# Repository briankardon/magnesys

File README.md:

# Magnesys

A Python-based magnetic field simulator with an interactive 3D visualization GUI.

## Features

### Simulation
- **Exact analytical solutions** for circular loops using complete elliptic integrals (machine precision, no numerical integration)
- **Biot-Savart integration** for arbitrary wire geometries (rounded rectangles, extensible to any shape)
- **Arbitrary orientations** — current loops can be placed and oriented anywhere in 3D space
- **Time-varying fields** — each current source has frequency and phase parameters; field modulated by cos(2πft + φ) at any time t
- **Vectorized computation** — field evaluation works on single points or NumPy meshgrids
- **Extensible geometry** — abstract `CurrentLoop` base class with a registration system for adding new loop shapes

### Visualization
- **Interactive 3D viewer** powered by PyVista + Qt, with pan/rotate/zoom
- **Quiver plot** of the magnetic field with three arrow scaling modes (uniform, logarithmic, linear), selectable via radio buttons
- **Draggable slice plane** — compute and display the field on an arbitrary 2D cross-section
- **Sample paths with 2D plot** — three path types (line segment, polyline, spline) with draggable 3D handles; two plot modes: "B vs. position" (field along path at current time) and "B vs. time" (simulated sensor moving along path); dropdown to select which path is displayed
- **Current direction indicators** — arrowheads on each loop showing the direction of current flow
- **Near-wire filtering** — points too close to the wire (where the thin-wire model diverges) are automatically excluded from visualization and color scaling

### GUI controls
- **Objects tree view** — unified list of loops and sample paths with editable properties (double-click to edit). Vectors expand into individual x/y/z components. Changes update the 3D view in real time.
- **Add/delete objects** — Edit menu to add loops (circular, rounded rectangle, infinite line) and paths (line segment, polyline, spline). Delete or clear all via Edit menu, right-click context menu, or Delete key. Polyline/spline points can be added, deleted, or randomized via right-click.
- **Time slider** — scrub through time to see AC fields oscillate; auto-ranges to one period of the slowest frequency
- **Grid resolution slider** with live spacing readout in cm/mm
- **Auto-update toggle** — disable for expensive simulations, use the Update button manually
- **Auto-scale toggle** — lock 3D color bar, arrow lengths, and 2D y-axis to see time-varying amplitude changes
- **Arrow scaling radio buttons** — switch between uniform, logarithmic (default), and linear

### Project files
- **`.mag` file format** (v3) — human-readable JSON storing simulation, visualization settings, camera position, slice plane state, and multiple sample paths
- **File menu** — Open (Ctrl+O), Save (Ctrl+S), Save As (Ctrl+Shift+S)
- **Export menu** — Export field along path to CSV with configurable sampling interval
- Backward-compatible with v1 (simulation-only) and v2 (single sample path) files

## Supported Geometries

| Type | Class | Field method | Parameters |
|------|-------|-------------|------------|
| Circular loop | `CircularCurrentLoop` | Elliptic integrals (exact) | diameter, center, normal, current, frequency, phase |
| Rounded rectangle | `RoundRectCurrentLoop` | Biot-Savart (numerical) | side_lengths, corner_radius, center, normal, orientation, current, frequency, phase |
| Infinite line | `InfiniteLineCurrent` | Analytical (exact) | center, normal, current, frequency, phase |

## Installation

Requires Python 3.10+.

```bash
py -3.14 -m venv .venv
.venv/Scripts/activate    # Windows
pip install numpy scipy pyvista pyvistaqt PyQt6 pyqtgraph
```

## Usage

### GUI

```bash
# Launch with empty simulation
python magnesys.py

# Open a project file
python magnesys.py demos/helmholtz_coil.mag
```

In the GUI you can:
- **Add loops** via Edit → Add loop → Circular / Rounded rectangle / Infinite line
- **Add sample paths** via Edit → Add path → Line segment / Polyline / Spline
- **Edit properties** by double-clicking values in the Objects tree view
- **Delete objects** by selecting one and pressing Delete (or right-click → Delete)
- **Edit polyline/spline points** — right-click a point for Add before/after, Delete, or Randomize
- **Adjust the field grid** with the resolution slider
- **Enable a slice plane** to see the field on a 2D cross-section (draggable)
- **Show sample paths** to plot Bx, By, Bz, |B| vs distance; select path via dropdown
- **Export field data** along the selected path to CSV via Export → Export field along path
- **Save/open projects** as `.mag` files preserving all settings and camera position

### Python API

```python
import numpy as np
from source import CircularCurrentLoop, RoundRectCurrentLoop, Simulation, Visualizer

# Helmholtz coil pair
R = 0.05
sim = Simulation([
    CircularCurrentLoop(
        diameter=2 * R,
        center=[0, 0, R / 2],
        normal=[0, 0, 1],
        current=1.0,
    ),
    CircularCurrentLoop(
        diameter=2 * R,
        center=[0, 0, -R / 2],
        normal=[0, 0, 1],
        current=1.0,
    ),
])

# Compute field at a point
Bx, By, Bz = sim.magnetic_field_at(0, 0, 0)

# Compute field on a grid
X, Y, Z = np.meshgrid(
    np.linspace(-0.1, 0.1, 50),
    np.linspace(-0.1, 0.1, 50),
    [0.0],
)
Bx, By, Bz = sim.magnetic_field_on_grid(X, Y, Z)

# Open the interactive 3D viewer
Visualizer(sim).show(grid_resolution=8)

# Save / load
sim.save("my_simulation.json")
sim = Simulation.load("my_simulation.json")
```

## Demos

The `demos/` directory contains example scripts and `.mag` project files:

| Demo | Description |
|------|-------------|
| `helmholtz_coil` | Classic Helmholtz pair — nearly uniform field between coils |
| `anti_helmholtz` | Opposing currents — field gradient with zero at center |
| `mixed_geometries` | Circular + rectangular loops in one simulation |
| `tilted_loops` | Three orthogonal coils (3-axis coil system) |
| `rectangular_coil` | Sharp-cornered rectangle with save/load roundtrip |
| `rect_helmholtz_3axis` | Three pairs of rectangular Helmholtz coils |
| `field_along_line` | Sample line with 2D field plot |
| `showcase` | Multiple geometries, path types, and features |
| `ac_gradient_coils` | 3-axis anti-Helmholtz gradient coils at 100/137/173 Hz |
| `inversion_test_1kHz_5A` | 3-axis setup optimized for position inversion (1 kHz, 5A) |

Run any demo as a script or open the `.mag` file:

```bash
python demos/helmholtz_coil.py
python magnesys.py demos/helmholtz_coil.mag
```

## Position Inversion

Magnesys includes a magnetic-field-to-position inversion pipeline for
reconstructing a sensor's trajectory from its magnetometer readings.
This is designed for multi-frequency AC excitation setups (e.g. 3-axis
anti-Helmholtz gradient coils at coprime frequencies), where lock-in
demodulation separates each coil pair's contribution.

### How it works

1. **Lock-in demodulation** extracts each frequency's 3-axis field vector from the time-domain signal
2. **Coarse search** finds the nearest match in a precomputed field table (KD-tree)
3. **Nonlinear refinement** via `scipy.optimize.least_squares` from the coarse estimate
4. **6-DOF mode** jointly solves for position + orientation when the sensor rotates

### Workflow: magnesys → invert.py → magnesys

**1. Open a coil setup** with AC sources:
```bash
python magnesys.py demos/inversion_test_1kHz_5A.mag
```

**2. Create or edit a sample path** — this is the probe trajectory the synthetic sensor will follow.

**3. Export the synthetic signal** via Export → Export field vs. time:
- Select the path, set probe speed, duration, and sampling rate (≥10× highest frequency)
- Optionally check "Apply random sensor rotation" for 6-DOF testing
- Save as CSV (e.g. `my_signal.csv`)

**4. Run the inversion:**
```bash
python invert.py demos/inversion_test_1kHz_5A.mag my_signal.csv --window-periods 30
```
This prints position/orientation error statistics and writes `my_signal_inverted.csv`.

Options:
- `--resolution 35` — finer field table grid (slower, more accurate)
- `--window-periods 30` — demodulation window in periods of the lowest frequency

**5. Import the reconstructed trajectory** back into magnesys:
Edit → Import trajectory CSV → select `my_signal_inverted.csv`

**6. Compare** — the reconstructed trajectory appears alongside the original path in the 3D view.

### Tested accuracy (0.5m cage, MLX90393 sensor noise)

| Mode | Drive current | Position error (median) |
|------|--------------|------------------------|
| 3-DOF (no rotation) | 5 A | 2.2 mm |
| 6-DOF (30° rotation) | 5 A | 4.1 mm |

See `docs/inversion_log.md` for the full experiment history.

### Sensor profiles

The export dialog and `invert.py` both understand named sensor profiles
(`source/sensor_profile.py`).  A profile pairs a noise spectral density
(nT/√Hz) with a max 3-axis ODR (Hz); per-sample σ is computed from
`σ = N₀ · √(fs/2)` with `fs` clamped to the sensor's max ODR.  Picking
a profile in the Export → Field vs. time dialog automatically clamps the
sample-rate spinner and shows the resulting σ live.

| Profile | Tech | Noise (nT/√Hz) | Max ODR (Hz) | Notes |
|---------|------|---------------:|-------------:|-------|
| `ideal` | — | 0 | ∞ | Noiseless reference |
| `MLX90393` | Hall | 150 | 500 | Cannot support 1 kHz lock-in |
| `MLX90394` | Hall | 70 | 1000 | Lower-noise successor |
| `AK09940A` | TMR | 30 | 2500 | Best digital integrated option |
| `MMC5983MA` | AMR | 100 | 1000 | Similar regime to MLX90393 |
| `RM3100` | mag-induct. | 13 | 430 | Lowest noise, but heavy & slow |
| `DRV425x3` | fluxgate | 1.5 | 47000 | Reference-grade; high power |

List from the CLI:
```bash
python invert.py --list-sensors
```

Annotate an inversion run with the expected σ for a given profile:
```bash
python invert.py --sensor AK09940A project.mag signal.csv
```

Numbers are best-effort estimates from public datasheets — refine
against the operating mode (OSR, drive current, cycle count) you
actually plan to use.

### Reproducing experiments

`docs/inversion_log.md` is a chronological log of inversion experiments
(coil-geometry sweeps, frequency/window sweeps, sensor noise, dual-
sensor and trajectory studies). Experiments 1-14 were one-off
development work; the parameters are documented in the log but the
exact scripts weren't committed at the time. Experiments 15 onward have
self-contained, re-runnable scripts under `demos/`.

| Exp | Topic | Reproduce |
|----:|-------|-----------|
|  1  | Initial 3-DOF inversion (12 cm scale)  | no committed script — see log for parameters |
|  2  | Frequency grouping fix                  | no committed script |
|  3  | Window length sweep (stationary)        | no committed script |
|  4  | Moving trace, 3-period window           | no committed script |
|  5  | Current strength scaling                | no committed script |
|  6  | First 6-DOF inversion + SVD init        | no committed script |
|  7  | 4-DOF + IMU tilt                        | no committed script |
|  8  | Cage scale baseline (0.5 m)             | no committed script |
|  9  | Coil geometry sweep                     | no committed script |
| 10  | Multipass inversion                     | no committed script |
| 11  | Excitation frequency sweep              | no committed script |
| 12  | Orientation-first 6-DOF                 | no committed script |
| 13  | Fixed window duration, varying freq.    | no committed script |
| 14  | Noise injection (1 kHz, 0.5 m cage)     | no committed script — was the motivation for `SensorProfile` (Exp 15+) |
| 15  | Sensor-realistic re-run at 1 m cube     | `python demos/experiment_15_sensor_realistic.py` |
| 16  | Analog frontend recovers 1 kHz lock-in  | `python demos/experiment_16_analog_frontend.py` |
| 17  | Smaller cage (0.75 m), same coils       | `python demos/experiment_17_smaller_cage.py` |
| 18  | Dual-magnetometer backpack              | `python demos/experiment_18_dual_magnetometer.py` |
| 19  | Lissajous trajectory, robust 6-DOF init | `python demos/experiment_19_lissajous_trajectory.py` |

Most experiment scripts accept `--quick` for a fast lower-resolution
pass and `--duration N` to override the trajectory length. See each
script's `--help` for the full set of flags.

## Adding New Geometries

For geometries with closed-form field solutions, subclass `CurrentLoop` directly:

```python
@CurrentLoop.register
class MyLoop(CurrentLoop):
    loop_type = "my_loop"
    def magnetic_field(self, x, y, z): ...
    def distance_to_wire(self, x, y, z): ...
    def characteristic_size(self): ...
    def get_path(self, n_points=128): ...
    def to_dict(self): ...
    @classmethod
    def from_dict(cls, data): ...
```

For arbitrary wire shapes, subclass `PathBasedLoop` instead — just implement `get_path()` and serialization, and the Biot-Savart field computation is provided automatically.

## Architecture

```
magnesys.py                      # GUI launcher
invert.py                        # CLI for magnetic → position inversion
source/
    current_loop.py              # Abstract base class + registry
    circular_current_loop.py     # Exact field via elliptic integrals
    infinite_line_current.py     # Exact field for infinite straight wire
    path_based_loop.py           # Biot-Savart base for arbitrary paths
    round_rect_current_loop.py
    path.py                      # SamplePath / LineSegmentPath / PolylinePath / SplinePath
    trajectory.py                # Static 3D trajectory for visualization
    simulation.py                # Loop collection + field computation
    inversion.py                 # Field table, demodulation, position inversion
    sensor_profile.py            # Named sensor profiles (noise SD + max ODR)
    visualization.py             # Qt GUI + PyVista 3D + pyqtgraph 2D
    project.py                   # .mag file I/O
demos/
    *.py                         # Example scripts
    *.mag                        # Loadable project files
docs/
    inversion_log.md             # Experiment history and results
```

## Credits

Developed by **Brian Kardon** and **Claude** (Anthropic).

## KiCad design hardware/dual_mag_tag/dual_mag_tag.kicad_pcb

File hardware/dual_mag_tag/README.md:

# Magnesys Dual-Magnetometer Bird Tag — Schematic Design

This directory contains the schematic-level description of the
dual-magnetometer backpack tag developed in the inversion experiments
(see `docs/inversion_log.md`, Exps. 18-19). The design is the analog
TMR + AD8421 + nRF52832 SAADC chain with a 3 cm baseline between the
two magnetometers.

Files:

- `magnesys_dual_mag_tag.net` — KiCad netlist (S-expression `.net`
  format) listing all components and their net connections. This can
  be imported into KiCad's Pcbnew via *File → Import → Netlist*, or
  used as a reference when capturing the schematic in Eeschema.
- `magnesys_tag.kicad_sym` — KiCad symbol library with 6 custom
  schematic symbols: `AD8421`, `TLV9001`, `MIC5219-3.3YM5`,
  `NVE_AAH002` (single-axis analog GMR/TMR), `TMR_3AXIS_PLACEHOLDER`
  (generic 8-pin), and `nRF52832_MODULE` (13-pin module breakout
  with named pins).
- `README.md` (this file) — human-readable design description and BOM.

### Adding the symbol library to KiCad

1. *Preferences → Manage Symbol Libraries → Project Specific Libraries
   → Add an existing library to the table* (the folder icon).
2. Browse to `magnesys_tag.kicad_sym` and select it.
3. Give it a nickname (e.g., `magnesys_tag`).
4. Click *OK*. The 6 symbols become available under that nickname in
   the symbol chooser.

## High-level architecture

```
                     +--------- 3.7 V Li-ion battery (BT1)
                     |
                  +--+--+
                  | LDO | (U_LDO, 3.3 V)
                  +--+--+
                     |
       VCC = 3.3 V --+--------------+----------+----------+
                                    |          |          |
       REF = VCC/2 --+              |          |          |
                     |          +---+---+  +---+---+  ... (×8)
                     |          | TMR1  |  | AD8421|  ...
                     |          | (3-ax)|  | inamp |
       GND ----------+----------+---+---+  +---+---+  ...
                                |              |
                                |              v
                                | -- AC coup --> bias to REF --> +/-IN
                                |
                                +-- 3 cm baseline -- TMR2 same chain

       6 amp outputs --> R-C anti-alias --> nRF52832 SAADC inputs
                                            P0.02-0.05, P0.28-0.29
```

## Sections of the design

### Power

| Net  | Description                  |
|------|------------------------------|
| VBAT | Raw Li-ion (3.0–4.2 V)       |
| VCC  | LDO output, 3.3 V regulated  |
| GND  | Ground reference             |
| REF  | VCC/2, mid-supply for in-amp |

- `U_LDO` — 3.3 V LDO regulator (e.g., MIC5219-3.3 or ADP7142). Low
  quiescent current matters for battery life.
- `C_IN_LDO`, `C_OUT_LDO` — input and output bulk decoupling (1 µF
  ceramic each).
- `R_REF1`, `R_REF2` — divider from VCC to GND, 10 kΩ each, generates
  REF = VCC/2 ≈ 1.65 V.
- `C_REF` — 100 nF smoothing on the REF node.
- `U_BUF` — TLV9001 (or similar rail-to-rail single op-amp) wired as
  a unity-gain buffer to drive REF with low impedance. Without this,
  the REF node would be 5 kΩ Thevenin and would couple noise/offset
  through the in-amp REF pins.

### Magnetometers (×2)

`U_MAG1` and `U_MAG2` are 8-pin analog TMR 3-axis magnetometer dies
(e.g., NVE AAL024 series — replace with the exact part you choose). Pin
allocation:

| Pin | Net |
|-----|-----|
| 1 (VCC) | VCC |
| 2 (GND) | GND |
| 3 (X+)  | MAG1_XP / MAG2_XP |
| 4 (X−)  | MAG1_XN / MAG2_XN |
| 5 (Y+)  | MAG1_YP / MAG2_YP |
| 6 (Y−)  | MAG1_YN / MAG2_YN |
| 7 (Z+)  | MAG1_ZP / MAG2_ZP |
| 8 (Z−)  | MAG1_ZN / MAG2_ZN |

Decoupling: one 100 nF ceramic per sensor, placed close to its VCC
pin.

PCB layout note (not in netlist): MAG1 and MAG2 should be placed
**3.0 cm apart along the PCB +x axis**, with the same orientation. PCB
position tolerance ~0.1 mm is well below the inversion's sensitivity
to the offset.

### Per-channel analog frontend (×6)

Six identical channels, one per (sensor, axis): MAG1_X, MAG1_Y, MAG1_Z,
MAG2_X, MAG2_Y, MAG2_Z. For channel `n`:

| Designator       | Function           | Value     |
|------------------|--------------------|-----------|
| `C_AC{n}P`       | AC-coupling cap on +IN leg | 1 µF |
| `C_AC{n}N`       | AC-coupling cap on −IN leg | 1 µF |
| `R_BIAS{n}P`     | +IN bias to REF    | 100 kΩ    |
| `R_BIAS{n}N`     | −IN bias to REF    | 100 kΩ    |
| `U_AMP{n}`       | AD8421 in-amp      |           |
| `R_GAIN{n}`      | Gain resistor (RG) | 100 Ω → G ≈ 100 |
| `C_AMP{n}`       | Amp decoupling     | 100 nF    |
| `R_AA{n}`        | Anti-alias R       | 10 kΩ     |
| `C_AA{n}`        | Anti-alias C       | 1 nF      |

Signal chain per channel:

```
MAGn_(axis)P --[C_AC*P]--+-- AD8421 +IN
                         |
                         +--[R_BIAS*P]-- REF

MAGn_(axis)N --[C_AC*N]--+-- AD8421 -IN
                         |
                         +--[R_BIAS*N]-- REF

AD8421 RG (pins 2,3): R_GAIN
AD8421 REF (pin 5):   REF
AD8421 V+ (pin 7):    VCC (with C_AMP decoupling to GND)
AD8421 V- (pin 8):    GND
AD8421 OUT (pin 6) --[R_AA]--+-- to MCU ADC pin
                              |
                              +--[C_AA]-- GND
```

Gain calculation: AD8421 gain G = 1 + 9.9kΩ / RG. With RG = 100 Ω,
G ≈ 100. Adjust based on final sensor sensitivity and ADC range.

Anti-alias cutoff: f_c = 1 / (2π · R_AA · C_AA) = 1 / (2π · 10k · 1n)
≈ 16 kHz, comfortably below the nRF52832's 50 kSPS Nyquist of 25 kHz
and far above the 1 kHz signal band.

### nRF52832 connection

`J_MCU` is a header connector for an nRF52832 module (e.g., a
Raytac MDBT42Q breakout, or a custom-laid module). Pin assignment:

| Header pin | Net          | nRF52832 GPIO | Function                |
|-----------:|--------------|---------------|-------------------------|
|  1         | VCC          | (VDD)         | 3.3 V supply            |
|  2         | GND          | (VSS)         | Ground                  |
|  3         | ADC_M1X      | P0.02 / AIN0  | MAG1 X-axis amp out     |
|  4         | ADC_M1Y      | P0.03 / AIN1  | MAG1 Y-axis amp out     |
|  5         | ADC_M1Z      | P0.04 / AIN2  | MAG1 Z-axis amp out     |
|  6         | ADC_M2X      | P0.05 / AIN3  | MAG2 X-axis amp out     |
|  7         | ADC_M2Y      | P0.28 / AIN4  | MAG2 Y-axis amp out     |
|  8         | ADC_M2Z      | P0.29 / AIN5  | MAG2 Z-axis amp out     |
|  9         | CAL_BTN      | P0.06         | Calibration button (active low) |
| 10         | LED_STATUS   | P0.07         | Status LED (active high) |
| 11         | SWDIO        | (SWDIO)       | SWD data                |
| 12         | SWCLK        | (SWCLK)       | SWD clock               |
| 13         | nRESET       | (RESET)       | Module reset            |

The module breakout is assumed to handle its own crystal, antenna
matching, and BLE-side decoupling internally. If you're laying out the
nRF52832 chip directly rather than using a module, refer to the Nordic
reference design.

### User-interaction parts

- `SW_CAL` — momentary push-button, one side to CAL_BTN, other to GND.
  Internal pull-up on P0.06 used (configured in firmware).
- `LED1` + `R_LED` — status LED with 330 Ω current limit on
  LED_STATUS.

## Bill of Materials (consolidated)

| Qty | Designator(s)        | Description                              | Suggested part           |
|----:|----------------------|------------------------------------------|--------------------------|
|   1 | BT1                  | Li-ion battery connector (2-pin, 1.25 mm pitch) | Molex 53261 series       |
|   1 | U_LDO                | 3.3 V LDO, low Iq                        | MIC5219-3.3YM5 or ADP7142|
|   1 | U_BUF                | Single op-amp, rail-to-rail              | TLV9001IDBVR             |
|   2 | U_MAG1, U_MAG2       | 3-axis analog TMR magnetometer           | NVE AAL024 (verify pins) |
|   6 | U_AMP1..U_AMP6       | Instrumentation amplifier                | AD8421ARZ                |
|   2 | C_IN_LDO, C_OUT_LDO  | 1 µF / 16 V / X7R / 0603                 |                          |
|  ~9 | C_AMP1..6 + C_REF + C_VCC | 100 nF / 25 V / X7R / 0402         |                          |
|  12 | C_AC1P..6N           | 1 µF / 25 V / X7R / 0603                 | film if low-distortion needed |
|   6 | C_AA1..6             | 1 nF / 50 V / C0G / 0402                 |                          |
|   2 | R_REF1, R_REF2       | 10 kΩ / 0.1 % / 0402                     | matched pair             |
|  12 | R_BIAS1P..6N         | 100 kΩ / 1 % / 0402                      |                          |
|   6 | R_GAIN1..6           | 100 Ω / 0.1 % / 0402                     |                          |
|   6 | R_AA1..6             | 10 kΩ / 1 % / 0402                       |                          |
|   1 | R_LED                | 330 Ω / 5 % / 0402                       |                          |
|   1 | LED1                 | LED, 0603, any color                     |                          |
|   1 | SW_CAL               | SMT tactile button                       | C&K KMR-series           |
|   1 | J_MCU                | 13-pin 0.1″ header                       |                          |

Total parts ≈ 70.  Mass on a 30 × 30 mm 4-layer 0.6 mm PCB plus an
nRF52832 module: roughly 1.5 g excluding battery — well within the
budgerigar 5 % rule.

## Importing into KiCad

The netlist file is `magnesys_dual_mag_tag.net`. To use it:

1. **As a starting point for schematic capture:** open KiCad,
   create a new project, then in Eeschema use the netlist as a
   checklist while drawing — the `(comp ...)` blocks list every
   component you need, and the `(nets ...)` block tells you which
   pins connect together.
2. **Direct import to PCB editor:** in Pcbnew, *File → Import →
   Netlist* and select the file. Pcbnew will populate the board with
   footprints (you may need to assign footprints first via the netlist
   file itself or via a separate footprint-association step).
3. **As reference only:** read the file directly as a text netlist;
   the component and net structure is human-readable.

The TMR sensor symbol is referenced as a generic 8-pin part
(`Connector_Generic:Conn_01x08` style). When you have your final
sensor part chosen, replace it with the matching footprint and
symbol.

## Design caveats / next steps

1. **Reference noise.** The REF node carries the in-amp reference for
   all 6 channels. Any noise here couples into all outputs, so the
   buffered REF (via U_BUF) and a healthy bypass cap matter. If REF
   noise turns out to dominate, consider a dedicated low-noise voltage
   reference IC (e.g., LT6655 — bigger and pricier but lower noise).
2. **Sensor SET/RESET pins.** Most TMR magnetometers don't need
   SET/RESET (unlike AMR), but if your final sensor pick does, those
   pins are not yet wired in this design — add them in the schematic
   capture pass.
3. **ESD protection.** Not included in the netlist. For a wearable
   tag handled by people, add TVS diodes on the SWD pins and battery
   input.
4. **Battery management.** This design assumes the battery is charged
   externally. If you want USB charging, add an MCP73831 or similar.
5. **Footprint assignment.** The netlist suggests footprints (SOIC-8
   for AD8421, SOT-23-5 for the LDO, etc.) but you should verify
   against your specific part numbers before tape-out.

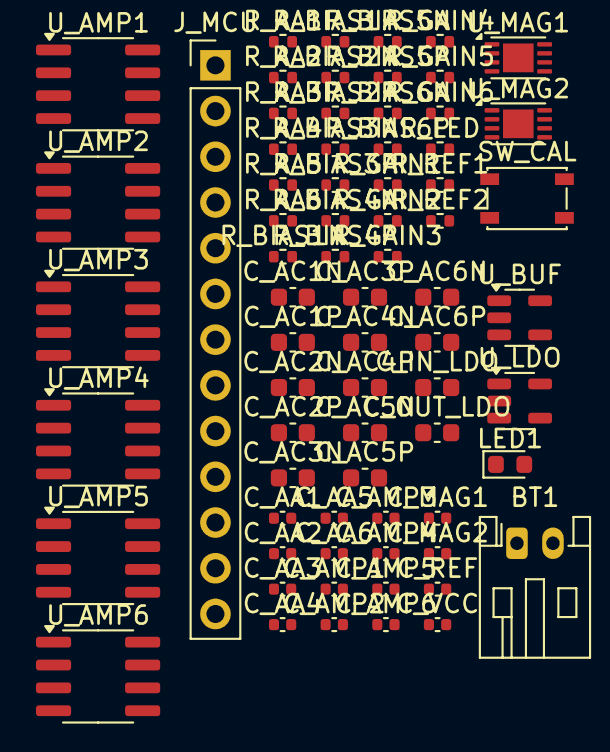
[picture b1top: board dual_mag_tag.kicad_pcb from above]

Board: 2 copper layers, 71 parts (0 on the bottom side), 56 nets, no tracks yet.

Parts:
BT1: Li-ion 3.7V; JST_PH_S2B-PH-K_1x02_P2.00mm_Horizontal
C_AA1, C_AA2, C_AA3, C_AA4, C_AA5, C_AA6: 1nF; C_0402_1005Metric
C_AC1N, C_AC1P, C_AC2N, C_AC2P, C_AC3N, C_AC3P, C_AC4N, C_AC4P, C_AC5N, C_AC5P, C_AC6N, C_AC6P: 1uF; C_0603_1608Metric
C_AMP1, C_AMP2, C_AMP3, C_AMP4, C_AMP5, C_AMP6: 100nF; C_0402_1005Metric
C_IN_LDO: 1uF; C_0603_1608Metric
C_MAG1, C_MAG2: 100nF; C_0402_1005Metric
C_OUT_LDO: 1uF; C_0603_1608Metric
C_REF: 100nF; C_0402_1005Metric
C_VCC: 100nF; C_0402_1005Metric
J_MCU: nRF52832 module; PinHeader_1x13_P2.54mm_Vertical
LED1: LED; LED_0603_1608Metric
R_AA1, R_AA2, R_AA3, R_AA4, R_AA5, R_AA6: 10k; R_0402_1005Metric
R_BIAS1N, R_BIAS1P, R_BIAS2N, R_BIAS2P, R_BIAS3N, R_BIAS3P, R_BIAS4N, R_BIAS4P, R_BIAS5N, R_BIAS5P, R_BIAS6N, R_BIAS6P: 100k; R_0402_1005Metric
R_GAIN1, R_GAIN2, R_GAIN3, R_GAIN4, R_GAIN5, R_GAIN6: 100R; R_0402_1005Metric
R_LED: 330R; R_0402_1005Metric
R_REF1, R_REF2: 10k 0.1%; R_0402_1005Metric
SW_CAL: TACT; SW_SPST_PTS810
U_AMP1, U_AMP2, U_AMP3, U_AMP4, U_AMP5, U_AMP6: AD8421; SOIC-8_3.9x4.9mm_P1.27mm
U_BUF: TLV9001; SOT-23-5
U_LDO: MIC5219-3.3YM5; SOT-23-5
U_MAG1, U_MAG2: TMR_3AXIS_ANALOG; DFN-8-1EP_3x2mm_P0.5mm_EP1.7x1.6mm

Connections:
ADC_M1X: C_AA1.1, J_MCU.3, R_AA1.2
ADC_M1Y: C_AA2.1, J_MCU.4, R_AA2.2
ADC_M1Z: C_AA3.1, J_MCU.5, R_AA3.2
ADC_M2X: C_AA4.1, J_MCU.6, R_AA4.2
ADC_M2Y: C_AA5.1, J_MCU.7, R_AA5.2
ADC_M2Z: C_AA6.1, J_MCU.8, R_AA6.2
AMP1_IN: C_AC1N.2, R_BIAS1N.1, U_AMP1.1
AMP1_IP: C_AC1P.2, R_BIAS1P.1, U_AMP1.4
AMP1_OUT: R_AA1.1, U_AMP1.6
AMP1_RG: R_GAIN1.1, U_AMP1.2
AMP1_RG2: R_GAIN1.2, U_AMP1.3
AMP2_IN: C_AC2N.2, R_BIAS2N.1, U_AMP2.1
AMP2_IP: C_AC2P.2, R_BIAS2P.1, U_AMP2.4
AMP2_OUT: R_AA2.1, U_AMP2.6
AMP2_RG: R_GAIN2.1, U_AMP2.2
AMP2_RG2: R_GAIN2.2, U_AMP2.3
AMP3_IN: C_AC3N.2, R_BIAS3N.1, U_AMP3.1
AMP3_IP: C_AC3P.2, R_BIAS3P.1, U_AMP3.4
AMP3_OUT: R_AA3.1, U_AMP3.6
AMP3_RG: R_GAIN3.1, U_AMP3.2
AMP3_RG2: R_GAIN3.2, U_AMP3.3
AMP4_IN: C_AC4N.2, R_BIAS4N.1, U_AMP4.1
AMP4_IP: C_AC4P.2, R_BIAS4P.1, U_AMP4.4
AMP4_OUT: R_AA4.1, U_AMP4.6
AMP4_RG: R_GAIN4.1, U_AMP4.2
AMP4_RG2: R_GAIN4.2, U_AMP4.3
AMP5_IN: C_AC5N.2, R_BIAS5N.1, U_AMP5.1
AMP5_IP: C_AC5P.2, R_BIAS5P.1, U_AMP5.4
AMP5_OUT: R_AA5.1, U_AMP5.6
AMP5_RG: R_GAIN5.1, U_AMP5.2
AMP5_RG2: R_GAIN5.2, U_AMP5.3
AMP6_IN: C_AC6N.2, R_BIAS6N.1, U_AMP6.1
AMP6_IP: C_AC6P.2, R_BIAS6P.1, U_AMP6.4
AMP6_OUT: R_AA6.1, U_AMP6.6
AMP6_RG: R_GAIN6.1, U_AMP6.2
AMP6_RG2: R_GAIN6.2, U_AMP6.3
CAL_BTN: J_MCU.9, SW_CAL.1
GND: BT1.2, C_AA1.2, C_AA2.2, C_AA3.2, C_AA4.2, C_AA5.2, C_AA6.2, C_AMP1.2, C_AMP2.2, C_AMP3.2, C_AMP4.2, C_AMP5.2, C_AMP6.2, C_IN_LDO.2, C_MAG1.2, C_MAG2.2, C_OUT_LDO.2, C_REF.2, C_VCC.2, J_MCU.2, LED1.1, R_REF2.2, SW_CAL.2, U_AMP1.8, U_AMP2.8, U_AMP3.8, U_AMP4.8, U_AMP5.8, U_AMP6.8, U_BUF.2, U_LDO.2, U_MAG1.2, U_MAG2.2
LED_ANODE: LED1.2, R_LED.2
LED_STATUS: J_MCU.10, R_LED.1
MAG1_XN: C_AC1N.1, U_MAG1.4
MAG1_XP: C_AC1P.1, U_MAG1.3
MAG1_YN: C_AC2N.1, U_MAG1.6
MAG1_YP: C_AC2P.1, U_MAG1.5
MAG1_ZN: C_AC3N.1, U_MAG1.8
MAG1_ZP: C_AC3P.1, U_MAG1.7
MAG2_XN: C_AC4N.1, U_MAG2.4
MAG2_XP: C_AC4P.1, U_MAG2.3
MAG2_YN: C_AC5N.1, U_MAG2.6
MAG2_YP: C_AC5P.1, U_MAG2.5
MAG2_ZN: C_AC6N.1, U_MAG2.8
MAG2_ZP: C_AC6P.1, U_MAG2.7
REF: R_BIAS1N.2, R_BIAS1P.2, R_BIAS2N.2, R_BIAS2P.2, R_BIAS3N.2, R_BIAS3P.2, R_BIAS4N.2, R_BIAS4P.2, R_BIAS5N.2, R_BIAS5P.2, R_BIAS6N.2, R_BIAS6P.2, U_AMP1.5, U_AMP2.5, U_AMP3.5, U_AMP4.5, U_AMP5.5, U_AMP6.5, U_BUF.1, U_BUF.4
REF_DIVIDER: C_REF.1, R_REF1.2, R_REF2.1, U_BUF.3
VBAT: BT1.1, C_IN_LDO.1, U_LDO.1, U_LDO.3
VCC: C_AMP1.1, C_AMP2.1, C_AMP3.1, C_AMP4.1, C_AMP5.1, C_AMP6.1, C_MAG1.1, C_MAG2.1, C_OUT_LDO.1, C_VCC.1, J_MCU.1, R_REF1.1, U_AMP1.7, U_AMP2.7, U_AMP3.7, U_AMP4.7, U_AMP5.7, U_AMP6.7, U_BUF.5, U_LDO.5, U_MAG1.1, U_MAG2.1

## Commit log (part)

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2026-03-20 Added 3-axis rectangular helmholtz demo
2026-03-20 Increase max grid resolution
2026-03-20 Minor fixes
    Accept v3 .mag files
    Fix zoom reset on grid resolution change
2026-03-22 Remove box outline around slice plane
